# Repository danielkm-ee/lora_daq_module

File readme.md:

# LoRA DAQ Node
For our Electrical and Computer Engineering practicum at Portland State for 2025 we have developed a LoRA based data acquisition node that can be used for data collection and monitoring systems over large areas.

This board is powered by the Seeed Studios Wio-E5 LoRA module for use with it's designated antenna.

## Supported Peripherals
We've done our best to provide a versatile range of peripherals for high quality data collection and application flexibility. This includes a UART interface for communicating with the device via it's USB-C port, a SWD interface for loading and debugging applications, a 16-bit ADC and I2C connector that can be used with analog and I2C compatible sensors.

The device may be powered via it's USB-C (USB 2.0) connection, or by a 1s1p lithium ion battery. The device also
supports battery charging when powered by USB-C with the battery connected.

List of Peripherals
------------------
* 16-bit ADC
* I2C interface
* MicroSD card slot
* 2 external UART interfaces (one via USB-C port)
* 6-pin SWD header for ST-Link v2
* SMA connector for the 868-916MHz LoRA Antenna
* 2-pin JST EH connector for battery power and charging

## Credits
* Manaf Alali - hardware schematics
* Eyad Ahmed  - firmware
* Daniel Monahan - hardware schematics and layout
* Saleh Sabti - hardware schematics
* Dingyu Zhou - firmware

> All team members contributed to every aspect of the project, going beyond the general roles specified here.

----
*Portland State University ECE411 Practicum project, Fall 2025*

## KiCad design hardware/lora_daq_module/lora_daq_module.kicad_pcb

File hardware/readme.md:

# LoRA DAQ Hardware
Here you will find the KiCAD project files for the lora daq module. This project has been separated into three main parts:  
* `adc.kicad_sch` includes the input filter and supporting hardware related to the adc  
* `power_management.kicad_sch` includes the battery controller, ldos, and dc-dc converters  
* `lora_module.kicad_sch` includes the wio-e5, lora antennae, and eeprom  

## KiCAD Version Control Notes (Please read these!)
KiCAD version control will be managed through this git repository, there are some important things to 
keep track of while you work!  

### Git Management
To keep things nice, please keep all of your work confined to the schematic for your module. This should also 
correspond to your git branch. Here's an example:

Say I'm working on the ADC, first I'll make a git branch for my work...
```
$ git checkout -b schematic-adc
Switched to a new branch 'schematic-adc'
```
then I'll do work in the adc.kicad_sch file, and when I'm ready to submit the updated schematic I'll upload it to
my schematic branch.
```
$ git add ./adc.kicad_sch
$ git commit -m "added buffer to the input filter of the ads1115"
$ git push --set-upstream origin schematic-adc
Enumerating objects: 22, done.
Counting objects: 100% (22/22), done.
Delta compression using up to 14 threads
Compressing objects: 100% (20/20), done.
Writing objects: 100% (20/20), 8.72 KiB | 4.36 MiB/s, done.
Total 20 (delta 5), reused 0 (delta 0), pack-reused 0
remote: Resolving deltas: 100% (5/5), completed with 1 local object.
remote: 
remote: Create a pull request for 'test' on GitHub by visiting:
remote:      https://github.com/danielkm-ee/lora_daq_module/pull/new/schematic-adc
remote: 
To github.com:danielkm-ee/lora_daq_module.git
 * [new branch]      schematic-adc -> schematic-adc
Branch 'schematic-adc' set up to track remote branch 'schematic-adc' from 'origin'.
```
This way I can push/pull changes to the adc schematic separately, so I can safely work on the adc schematic without 
the need to resolve merge conflicts.

### Symbol and footprint libraries
When you are creating KiCAD symbols, they will be stored in your local *project* directory. We want these files to 
stay local to your machine until we can all collectively incorporate them into a project symbol library, so we've set 
up the .gitignore file to prevent accidental uploads of your local kicad schematic files, this includes symbols, 
footprints, and project settings related to your local UI.

> #### Files to keep local:
> * `fp-info-cache` -- this helps kicad pull up your most recent footprints faster, this thing is disposable and kicad creates and replaces it automatically
> * all `*.pretty` files -- these are footprint library files, they group your local symbols into library groups
> * all `*.kicad_mod` files -- these are your actual footprints (called 'modern footprint files')

> It is important that these aren't added to your commits because they will cause merge conflicts.

You are free to create and manage your footprint and symbol libraries locally in any way you choose--try to be 
organized because it will help us create a shared symbol library.

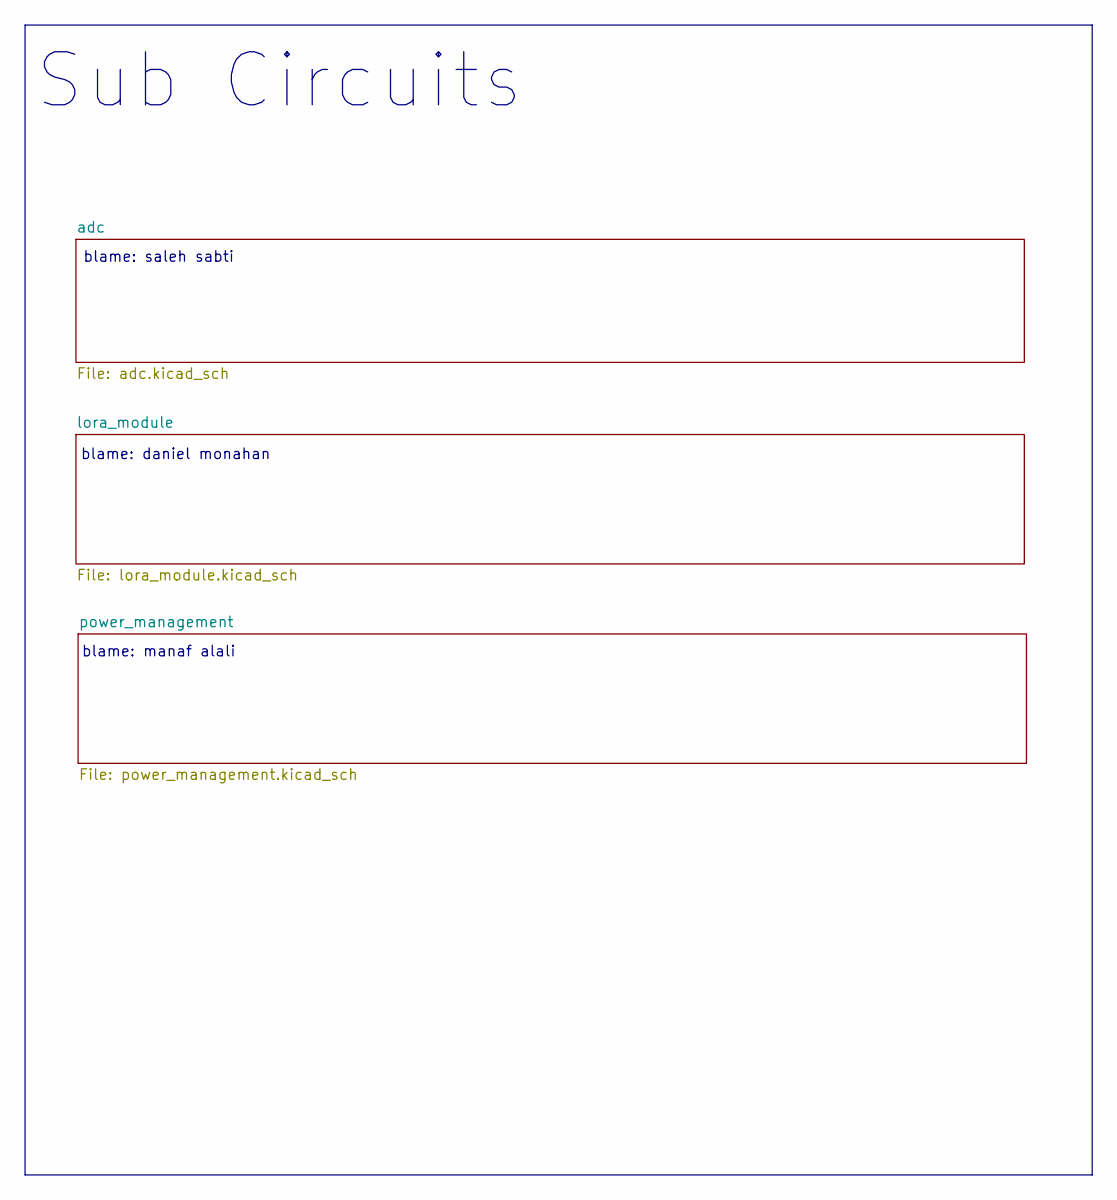
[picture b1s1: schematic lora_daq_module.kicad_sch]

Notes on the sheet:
blame: manaf alali
blame: saleh sabti
blame: daniel monahan
Sub Circuits

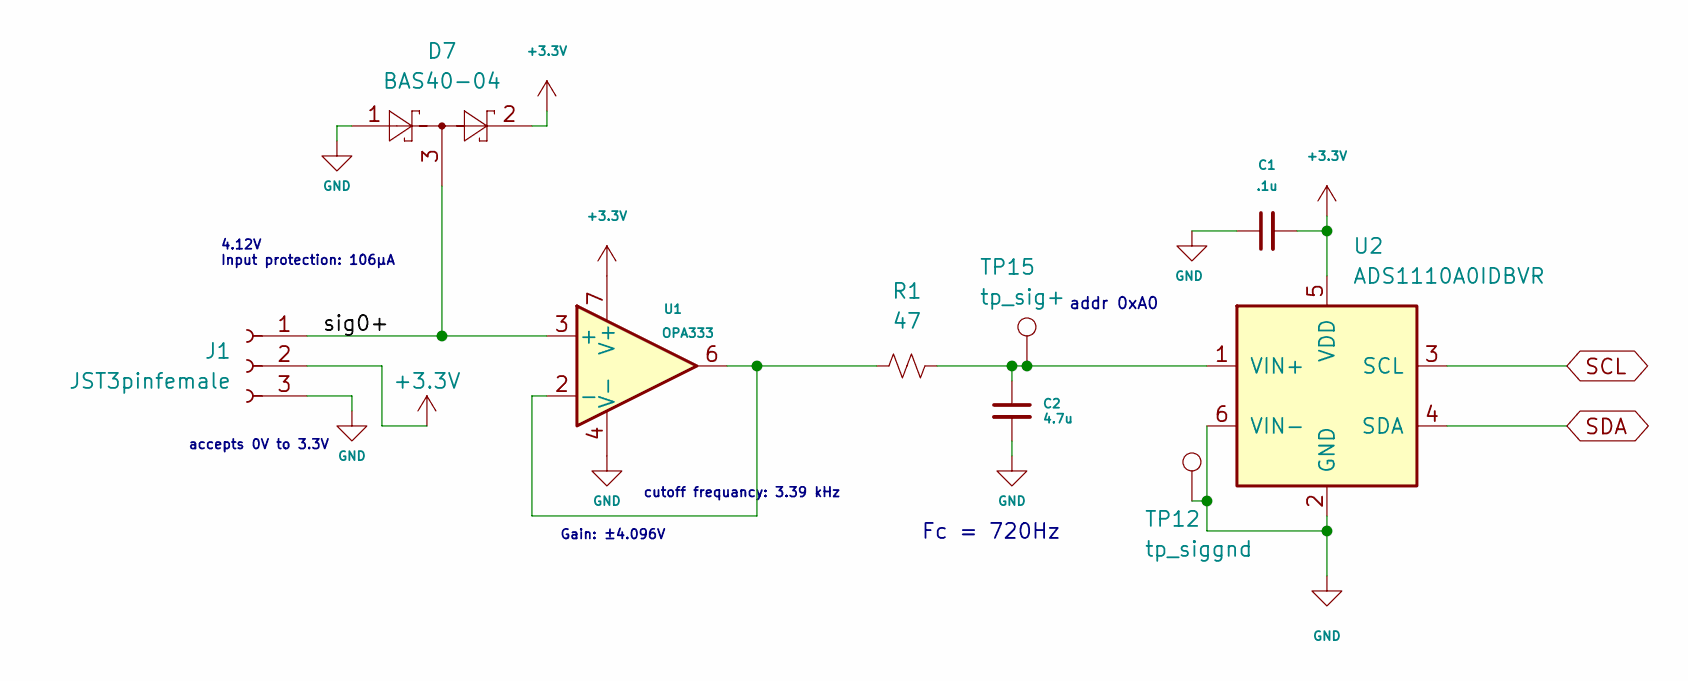
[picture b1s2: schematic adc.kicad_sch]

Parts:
C1: .1u; C_0603_1608Metric; Mfr PN CC0603KRX7R7BB104
C2: 4.7u; C_0603_1608Metric; Mfr PN CC0603KRX7R8BB473
D7: BAS40-04; SOT-23; Mfr PN BAS40-04
J1: JST3pinfemale; JST_EH_B3B-EH-A_1x03_P2.50mm_Vertical; Mfr PN B3B-EH-A
R1: 47; R_1206_3216Metric; Mfr PN RC1206FR-0747RL
TP12: tp_siggnd; TestPoint_THTPad_1.5x1.5mm_Drill0.7mm
TP15: tp_sig+; TestPoint_THTPad_1.5x1.5mm_Drill0.7mm
U1: OPA333; SOT-353_SC-70-5_Handsoldering; Mfr PN OPA333AIDCKR
U2: ADS1110A0IDBVR; SOT-23-6; Mfr PN ADS1110A0IDBVR

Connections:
+3.3V: C1.2, D7.2, J1.2, U1.7 (V+), U2.5 (VDD); also elsewhere on the board
/adc/sig0+: D7.3, J1.1, U1.3 (+)
GND: C1.1, C2.2, D7.1, J1.3, TP12.1, U1.4 (V-), U2.2 (GND), U2.6 (VIN-); also elsewhere on the board
unnamed: R1.1, U1.2 (-), U1.6
unnamed: C2.1, R1.2, TP15.1, U2.1 (VIN+)
SCL: U2.3 (SCL); also elsewhere on the board
SDA: U2.4 (SDA); also elsewhere on the board

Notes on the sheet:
addr 0xA0
cutoff frequancy: 3.39 kHz
accepts 0V to 3.3V
4.12V Input protection: 106µA
Gain: ±4.096V
Fc = 720Hz

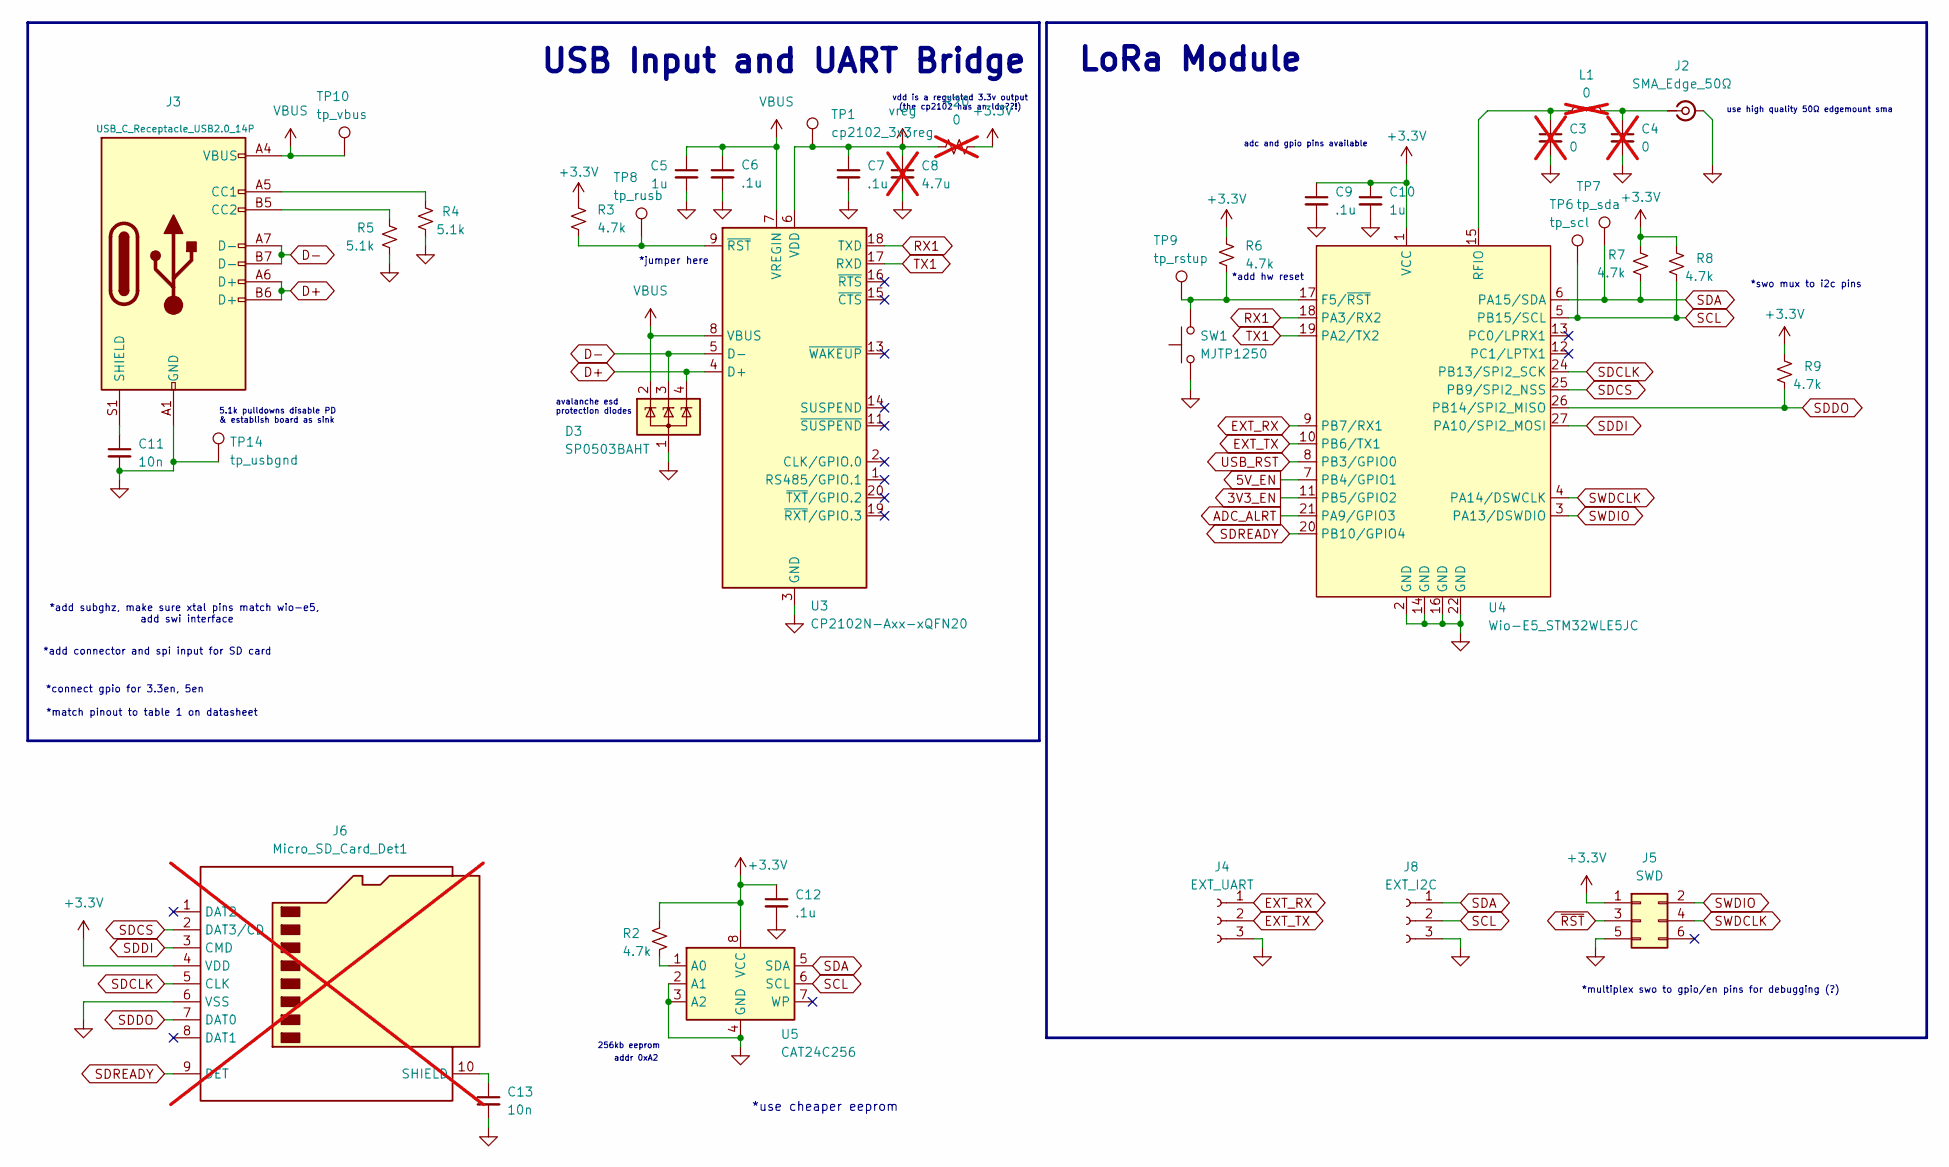
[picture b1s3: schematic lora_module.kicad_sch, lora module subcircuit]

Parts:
C3, C4: 0; C_0402_1005Metric; not fitted
C5, C10: 1u; C_0603_1608Metric; Mfr PN GCM188R71C105KA64D
C6, C7, C9, C12: .1u; C_0603_1608Metric; Mfr PN CC0603KRX7R7BB104
C8: 4.7u; C_1206_3216Metric; Mfr PN GRM31CR71H475KA12L; not fitted
C11, C13: 10n; C_0603_1608Metric; Mfr PN GCM188R72A103KA37D
D3: SP0503BAHT; SOT-143; Mfr PN SP0503BAHTG
J2: SMA_Edge_50Ω; SMA_Molex_73251-1153_EdgeMount_Horizontal; MPN CONSMA001-C-G
J3: USB_C_Receptacle_USB2.0_14P; USB_C_Receptacle_GCT_USB4105-xx-A_16P_TopMnt_Horizontal; Mfr PN USB4105-GF-A-120
J4: EXT_UART; JST_EH_B3B-EH-A_1x03_P2.50mm_Vertical; Mfr PN B3B-EH-A
J5: SWD; PinHeader_2x03_P2.54mm_Vertical; Mfr PN 61300621121
J6: Micro_SD_Card_Det1; microSD_HC_Molex_104031-0811; Mfr PN 1040310811; not fitted
J8: EXT_I2C; JST_EH_B3B-EH-A_1x03_P2.50mm_Vertical; Mfr PN B3B-EH-A
L1: 0; L_0402_1005Metric; Mfr PN RC0402JR-070RL; not fitted
R2, R3, R6, R7, R8, R9: 4.7k; R_0603_1608Metric; Mfr PN RC0603JR-074K7L
R4, R5: 5.1k; R_0603_1608Metric; Mfr PN RC0603FR-075K1L
R20: 0; R_0603_1608Metric; Mfr PN RMCF0603ZT0R00; not fitted
SW1: MJTP1250; SW_PUSH_1P1T_6x3.5mm_H5.0_APEM_MJTP1250; Mfr PN MJTP1250
TP1: cp2102_3v3reg; TestPoint_Pad_1.5x1.5mm
TP6: tp_scl; TestPoint_THTPad_1.5x1.5mm_Drill0.7mm
TP7: tp_sda; TestPoint_THTPad_1.5x1.5mm_Drill0.7mm
TP8: tp_rusb; TestPoint_THTPad_1.5x1.5mm_Drill0.7mm
TP9: tp_rstup; TestPoint_THTPad_1.5x1.5mm_Drill0.7mm
TP10: tp_vbus; TestPoint_THTPad_1.5x1.5mm_Drill0.7mm
TP14: tp_usbgnd; TestPoint_THTPad_1.5x1.5mm_Drill0.7mm
U3: CP2102N-Axx-xQFN20; SiliconLabs_QFN-20-1EP_3x3mm_P0.5mm_EP1.8x1.8mm; Mfr PN CP2102N-A02-GQFN20R
U4: Wio-E5_STM32WLE5JC; LoRa-E5; Mfr PN 317990829
U5: CAT24C256; SOIC-8-1EP_3.9x4.9mm_P1.27mm_EP2.29x3mm; Mfr PN CAT24C256WI-GT3

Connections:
3V3_EN: U4.11 (PB5/GPIO2)
5V_EN: U4.7 (PB4/GPIO1)
+3.3V: C9.1, C10.1, C12.1, J5.1, J6.4 (VDD), R2.2, R3.1, R6.1, R7.2, R8.2, R9.2, R20.2, U4.1 (VCC), U5.8 (VCC); also elsewhere on the board
ADC_ALRT: U4.21 (PA9/GPIO3)
D+: D3.4 (K), J3.A6 (D+), J3.B6 (D+), U3.4 (D+)
D-: D3.3 (K), J3.A7 (D-), J3.B7 (D-), U3.5 (D-)
EXT_RX: J4.1, U4.9 (PB7/RX1)
EXT_TX: J4.2, U4.10 (PB6/TX1)
GND: C3.2, C4.2, C5.2, C6.2, C7.2, C8.2, C9.2, C10.2, C11.2, C12.2, C13.2, D3.1 (A), J2.2 (Ext), J3.A1 (GND), J3.A12 (GND), J3.B1 (GND), J3.B12 (GND), J4.3, J5.5, J6.6 (VSS), J8.3, R4.1, R5.1, SW1.1, TP14.1, U3.3 (GND), U3.12 (GND), U3.21 (GND), U4.2 (GND), U4.14 (GND), U4.16 (GND), U4.22 (GND), U5.2 (A1), U5.3 (A2), U5.4 (GND); also elsewhere on the board
unnamed: C4.1, J2.1 (In), L1.2
unnamed: J3.A5 (CC1), R4.2
unnamed: J3.B5 (CC2), R5.2
unnamed: C11.1, J3.S1 (SHIELD)
unnamed: C13.1, J6.10 (SHIELD)
unnamed: R3.2, TP8.1, U3.9 (~RST)
unnamed: R6.2, SW1.2, TP9.1, U4.17 (F5/~RST)
unnamed: C3.1, L1.1, U4.15 (RFIO)
unnamed: R2.1, U5.1 (A0)
RX1: U3.18 (TXD), U4.18 (PA3/RX2)
SCL: J8.2, R8.1, U4.5 (PB15/SCL), U5.6 (SCL); also elsewhere on the board
SDA: J8.1, R7.1, U4.6 (PA15/SDA), U5.5 (SDA); also elsewhere on the board
SDCLK: J6.5 (CLK), U4.24 (PB13/SPI2_SCK)
SDCS: J6.2 (DAT3/CD), U4.25 (PB9/SPI2_NSS)
SDDI: J6.3 (CMD), U4.27 (PA10/SPI2_MOSI)
SDDO: J6.7 (DAT0), R9.1, U4.26 (PB14/SPI2_MISO)
SDREADY: J6.9 (DET), U4.20 (PB10/GPIO4)
SWDCLK: J5.4, U4.4 (PA14/DSWCLK)
SWDIO: J5.2, U4.3 (PA13/DSWDIO)
TX1: U3.17 (RXD), U4.19 (PA2/TX2)
USB_RST: U4.8 (PB3/GPIO0)
VBUS: C5.1, C6.1, D3.2 (K), J3.A4 (VBUS), J3.A9 (VBUS), J3.B4 (VBUS), J3.B9 (VBUS), TP10.1, U3.7 (VREGIN), U3.8 (VBUS); also elsewhere on the board
vreg: C7.1, C8.1, R20.1, TP1.1, U3.6 (VDD)
~RST: J5.3

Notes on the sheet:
vdd is a regulated 3.3v output (the cp2102 has an ldo??!)
*use cheaper eeprom
avalanche esd protection diodes
5.1k pulldowns disable PD & establish board as sink
*jumper here
*match pinout to table 1 on datasheet
*add hw reset
use high quality 50Ω edgemount sma
USB Input and UART Bridge
*swo mux to i2c pins
256kb eeprom
*add subghz, make sure xtal pins match wio-e5, add swi interface
addr 0xA2
*add connector and spi input for SD card
LoRa Module
*connect gpio for 3.3en, 5en
adc and gpio pins available
*multiplex swo to gpio/en pins for debugging (?)

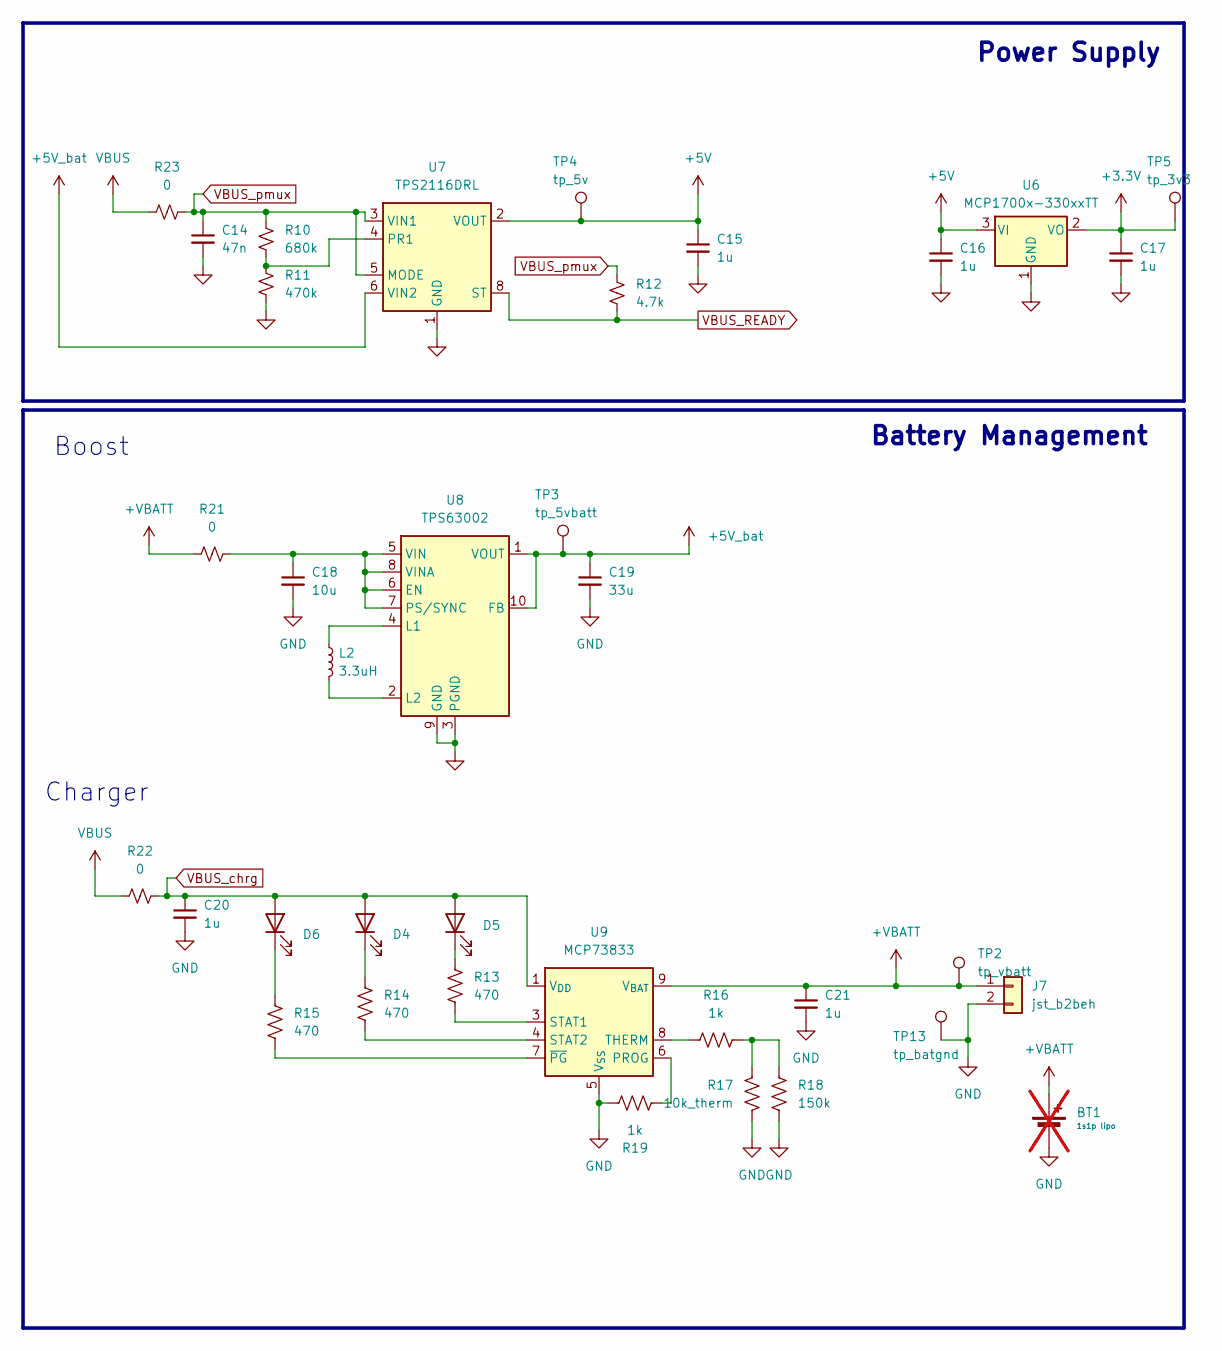
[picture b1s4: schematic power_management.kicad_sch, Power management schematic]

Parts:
BT1: 1s1p lipo; Mfr PN 258; not fitted
C14: 47n; C_0603_1608Metric; Mfr PN CC0603KRX7R8BB473
C15, C16, C17, C20, C21: 1u; C_0603_1608Metric; Mfr PN GCM188R71C105KA64D
C18: 10u; C_1206_3216Metric; Mfr PN CL31A106KBHNNNE
C19: 33u; C_1206_3216Metric; Mfr PN C3216JB1C336M160AB
D4: Green; LED_0603_1608Metric; Mfr PN LTST-C191KGKT
D5: Yellow; LED_0603_1608Metric; Mfr PN LTST-C191KSKT
D6: Red; LED_0603_1608Metric; Mfr PN LTST-C190KRKT
J7: jst_b2beh; JST_EH_B2B-EH-A_1x02_P2.50mm_Vertical; Mfr PN B2B-EH-A
L2: 3.3uH; L_Coilcraft_LPS3010; Mfr PN LPS3015-332MRC
R10: 680k; R_0603_1608Metric; Mfr PN RC0603FR-07680KL
R11: 470k; R_0603_1608Metric; Mfr PN RMCF0603FT470K
R12: 4.7k; R_0603_1608Metric; Mfr PN RC0603JR-074K7L
R13, R14, R15: 470; R_0603_1608Metric; Mfr PN RC0603JR-07470RL
R16, R19: 1k; R_0603_1608Metric; Mfr PN RMCF0603FT1K00
R17: 10k_therm; R_0603_1608Metric; Mfr PN NCU18XH103F60RB
R18: 150k; R_0603_1608Metric; Mfr PN RMCF0603FT150K
R21, R22, R23: 0; R_1812_4532Metric; Mfr PN ERJ-12Y0R00U
TP2: tp_vbatt; TestPoint_THTPad_1.5x1.5mm_Drill0.7mm
TP3: tp_5vbatt; TestPoint_THTPad_1.5x1.5mm_Drill0.7mm
TP4: tp_5v; TestPoint_THTPad_1.5x1.5mm_Drill0.7mm
TP5: tp_3v3; TestPoint_THTPad_1.5x1.5mm_Drill0.7mm
TP13: tp_batgnd; TestPoint_THTPad_1.5x1.5mm_Drill0.7mm
U6: MCP1700x-330xxTT; SOT-23; Mfr PN MCP1700T-3302E/TT
U7: TPS2116DRL; SOT-583-8; Mfr PN TPS2116DRLR
U8: TPS63002; Texas_DRC0010J_ThermalVias; Mfr PN TPS63002DRCR
U9: MCP73833; MSOP-10_3x3mm_P0.5mm; Mfr PN MCP73833T-AMI/UN

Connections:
+3.3V: C17.1, TP5.1, U6.2 (VO); also elsewhere on the board
+5V: C15.1, C16.1, TP4.1, U6.3 (VI), U7.2 (VOUT), U7.7 (VOUT)
+5V_bat: C19.1, TP3.1, U7.6 (VIN2), U8.1 (VOUT), U8.10 (FB)
+VBATT: BT1.1 (+), C21.1, J7.1, R21.1, TP2.1, U9.9 (V_{BAT}), U9.10 (V_{BAT})
GND: C14.2, C15.2, C16.2, C17.2, C18.2, C19.2, C20.2, C21.2, J7.2, R11.2, R17.2, R18.1, R19.1, TP13.1, U6.1 (GND), U7.1 (GND), U8.3 (PGND), U8.9 (GND), U8.11 (PGND), U9.5 (V_{SS}); also elsewhere on the board
unnamed: D4.1 (K), R14.1
unnamed: D5.1 (K), R13.1
unnamed: D6.1 (K), R15.1
unnamed: R16.2, R17.1, R18.2
unnamed: R10.2, R11.1, U7.4 (PR1)
unnamed: C18.1, R21.2, U8.5 (VIN), U8.6 (EN), U8.7 (PS/SYNC), U8.8 (VINA)
unnamed: L2.1, U8.4 (L1)
unnamed: L2.2, U8.2 (L2)
unnamed: R19.2, U9.6 (PROG)
unnamed: R13.2, U9.3 (STAT1)
unnamed: R14.2, U9.4 (STAT2)
unnamed: R16.1, U9.8 (THERM)
unnamed: R15.2, U9.7 (~PG)
VBUS: R22.1, R23.1; also elsewhere on the board
VBUS_READY: R12.2, U7.8 (ST)
VBUS_chrg: C20.1, D4.2 (A), D5.2 (A), D6.2 (A), R22.2, U9.1 (V_{DD}), U9.2 (V_{DD})
VBUS_pmux: C14.1, R10.1, R12.1, R23.2, U7.3 (VIN1), U7.5 (MODE)

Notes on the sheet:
Boost
Battery Management
Charger
Power Supply

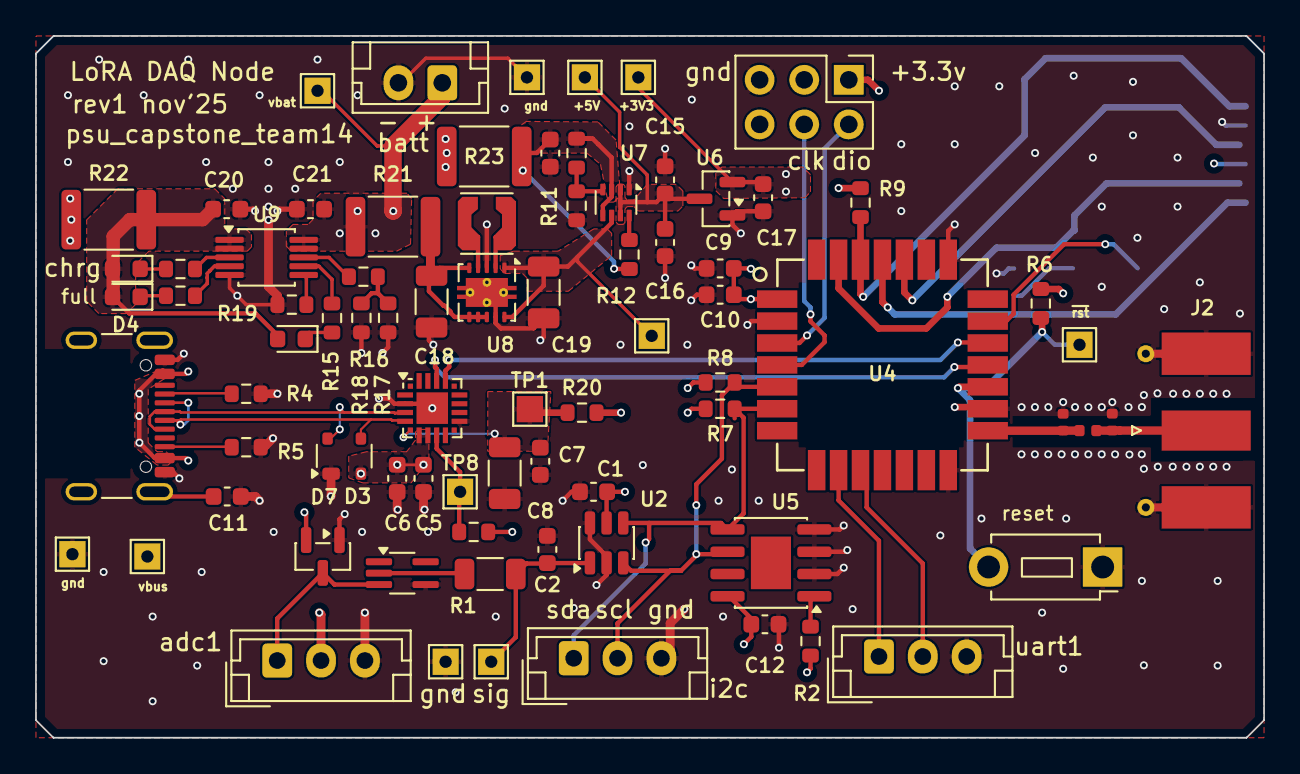
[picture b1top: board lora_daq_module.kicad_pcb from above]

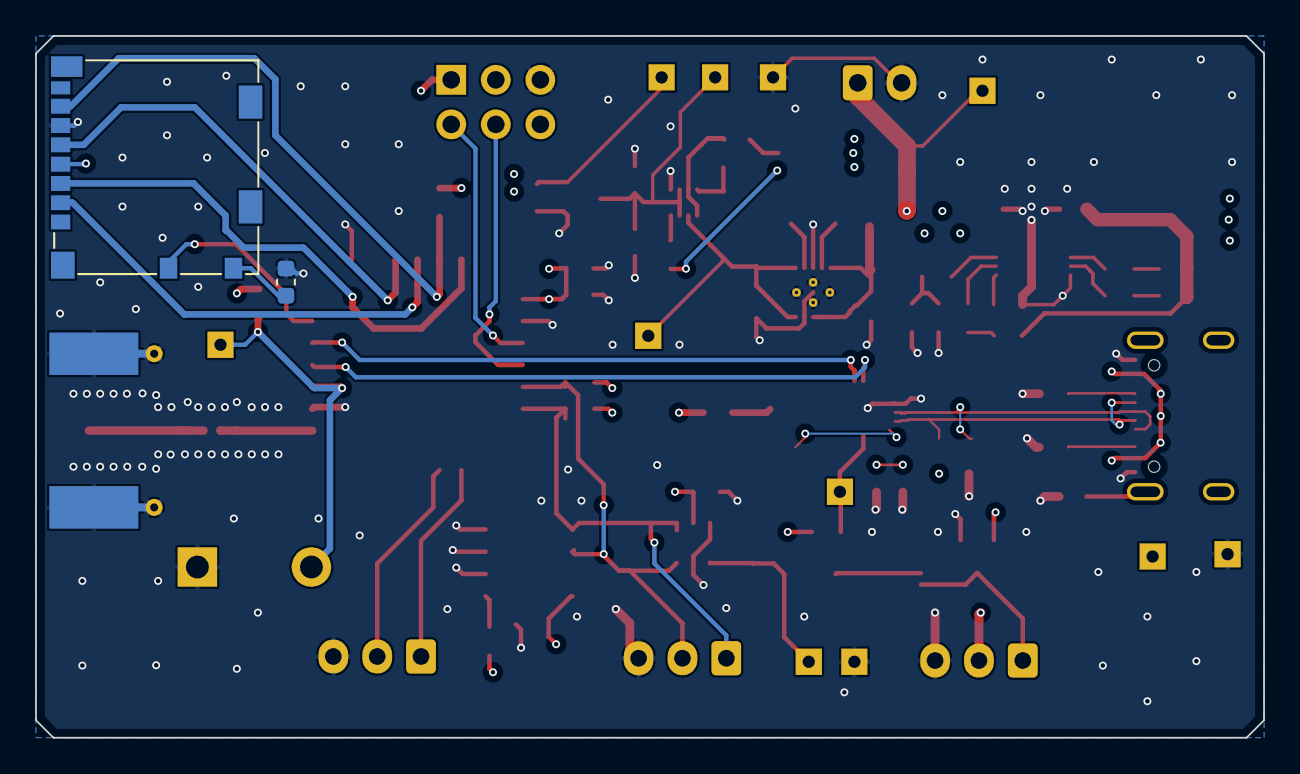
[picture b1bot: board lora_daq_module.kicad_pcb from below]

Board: 4 copper layers, 70.0 x 40.0 mm, 81 parts (2 on the bottom side), 50 nets.

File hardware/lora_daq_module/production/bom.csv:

Designator,Footprint,Quantity,Value,LCSC Part #
"C1, C12, C6, C7, C9",0603,5,.1u,
"C10, C15, C16, C17, C20, C21, C5",0603,7,1u,
"C11, C13",0603,2,10n,
C14,0603,1,47n,
C18,1206,1,10u,
C19,1206,1,33u,
C2,0603,1,4.7u,
C8,1206,1,4.7u,
D3,SOT-143,1,SP0503BAHT,
D4,0603,1,Green,
D5,0603,1,Yellow,
D6,0603,1,Red,
D7,SOT-23,1,BAS40-04,
J1,JST_EH_B3B-EH-A_1x03_P2.50mm_Vertical,1,JST3pinfemale,
J2,SMA_Molex_73251-1153_EdgeMount_Horizontal,1,SMA_Edge_50Ω,CONSMA001-C-G
J3,USB_C_Receptacle_GCT_USB4105-xx-A_16P_TopMnt_Horizontal,1,USB_C_Receptacle_USB2.0_14P,
J4,JST_EH_B3B-EH-A_1x03_P2.50mm_Vertical,1,EXT_UART,
J5,PinHeader_2x03_P2.54mm_Vertical,1,SWD,
J6,microSD_HC_Molex_104031-0811,1,Micro_SD_Card_Det1,
J7,JST_EH_B2B-EH-A_1x02_P2.50mm_Vertical,1,jst_b2beh,
J8,JST_EH_B3B-EH-A_1x03_P2.50mm_Vertical,1,EXT_I2C,
L1,0402,1,0,
L2,L_Coilcraft_LPS3010,1,3.3uH,
R1,1206,1,47,
R10,0603,1,680k,
R11,0603,1,470k,
"R12, R2, R3, R6, R7, R8, R9",0603,7,4.7k,
"R13, R14, R15",0603,3,470,
"R16, R19",0603,2,1k,
R17,0603,1,10k_therm,
R18,0603,1,150k,
R20,0603,1,0,
"R21, R22, R23",1812,3,0,
"R4, R5",0603,2,5.1k,
SW1,SW_PUSH_1P1T_6x3.5mm_H5.0_APEM_MJTP1250,1,MJTP1250,
TP10,TestPoint_THTPad_1.5x1.5mm_Drill0.7mm,1,tp_vbus,
TP12,TestPoint_THTPad_1.5x1.5mm_Drill0.7mm,1,tp_siggnd,
TP13,TestPoint_THTPad_1.5x1.5mm_Drill0.7mm,1,tp_batgnd,
TP14,TestPoint_THTPad_1.5x1.5mm_Drill0.7mm,1,tp_usbgnd,
TP15,TestPoint_THTPad_1.5x1.5mm_Drill0.7mm,1,tp_sig+,
TP2,TestPoint_THTPad_1.5x1.5mm_Drill0.7mm,1,tp_vbatt,
TP3,TestPoint_THTPad_1.5x1.5mm_Drill0.7mm,1,tp_5vbatt,
TP4,TestPoint_THTPad_1.5x1.5mm_Drill0.7mm,1,tp_5v,
TP5,TestPoint_THTPad_1.5x1.5mm_Drill0.7mm,1,tp_3v3,
TP8,TestPoint_THTPad_1.5x1.5mm_Drill0.7mm,1,tp_rusb,
TP9,TestPoint_THTPad_1.5x1.5mm_Drill0.7mm,1,tp_rstup,
U1,SOT-353_SC-70-5_Handsoldering,1,OPA333,
U2,SOT-23-6,1,ADS1110A0IDBVR,
U3,SiliconLabs_QFN-20-1EP_3x3mm_P0.5mm_EP1.8x1.8mm,1,CP2102N-Axx-xQFN20,
U4,LoRa-E5,1,Wio-E5_STM32WLE5JC,
U5,SOIC-8-1EP_3.9x4.9mm_P1.27mm_EP2.29x3mm,1,CAT24C256,
U6,SOT-23,1,MCP1700x-330xxTT,
U7,SOT-583-8,1,TPS2116DRL,
U8,Texas_DRC0010J_ThermalVias,1,TPS63002,
U9,MSOP-10_3x3mm_P0.5mm,1,MCP73833,

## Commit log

2025-10-09 inital commit, add project structure/readmes
2025-10-09 add firmware structure
2025-10-09 add prelim license
2025-10-09 update license
2025-10-16 add .gitignore to prevent local kicad configs which will cause merge issues
2025-10-16 add *-backups to git ignore
2025-10-16 add kicad project files
2025-10-16 add idea for kicad version control to readme
2025-10-16 add docs folder for dev notes and other official stuff
2025-10-16 update schematic properties
2025-10-21 add dev notes for adc integration
2025-10-21 add dev notes for power schematic
2025-10-24 add chips and start wiring USBC Recept. & UART bridge
2025-10-24 added eeprom support, antenna connector, and general connections needed for rev0 schematic
2025-10-24 schematic documentation
2025-10-27 added ADC input filter schematic
2025-10-27 added Oct 26 ADC KiCad schematic design notes
2025-10-28 added Oct 26 ADC schematic design log
2025-10-28 added the mcp73833
2025-10-29 added the tps63001 and tps63002 with their reference design
2025-10-30 Updated the Adc circuit w/filters
2025-11-11 docs: voltage divider optimization notes Nov 10
2025-11-11 modified ADC input filter schematic
2025-11-11 post design review comments
2025-11-12 initial commit of working toolchain
2025-11-12 clean up readme
2025-11-12 adjusted ADC input filter power rails, added commets
2025-11-12 add pinout for wio-e5 and add entry about schematic revisions to the dev note
2025-11-12 add sd card, swd connector, external uart, and update pinout for wio-e5
2025-11-12 add kicad symbol for wio-e5
2025-11-12 Removed the 3.3V buck-boost converter from the original design, then added LDO
2025-11-12 remove backups from repo
2025-11-13 update dev notes, add prelim layout pdf, prelim layout cad as pngs, and updated schematic as pdf
2025-11-13 add library for wio-e5 (from seeed studio, does not include custom wio-e5 symbol)
2025-11-13 updated power schematic to include power switching IC for battery/usb power, minor changes to lora module schematic, added footprints to all component and began with the preliminary layout based on d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
2025-11-13 update readme and description
2025-11-13 setup BOM columns
2025-11-14 add preliminary bom as xlsx, update dev notes regarding bom decision making process
2025-11-14 assign parts and update BOM in symbol field table, warn: pcb footprints need update
2025-11-14 add prelim bom as csv for native viewing on github
2025-11-15 solve strange Makefile problems
2025-11-16 add functional_decomposition doc
2025-11-16 near-complete layout of power domain
2025-11-17 lay traces to all components
2025-11-17 finish rough layout, drc fixedup
2025-11-17 add pdf captures of rough layout
2025-11-17 add rough draft schematic
2025-11-18 add test points and antenna microstrip
2025-11-18 add notes regarding antenna microstrip design
2025-11-20 add FreeRTOS lib
2025-11-20 edit board setup for jlcpcb 4 layer 1.6mm 1oz copper in/out and redesign antenna microstrip
2025-11-20 add ohm resistors for power schematic, update design rules for jlc
2025-11-21 add pcb final revision dev notes
2025-11-21 add final schematics, layout, 3dmodels
2025-11-21 add 0Ω resistors for disabling power circuits, revise adc input buffer and filter based on design review feedback, revise microstrip trace, add hardware reset button, add i2c connector and jst recept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
2025-11-21 add production files used for jlc order
2025-11-22 add rough draft of project readme
2025-11-22 update rough draft of readme
2025-11-25 adopting lora module from offical repo
2025-11-27 fix: strange compile issue after adding FreeRTOS, decide to test without FreeRTOS.
2025-12-01 enable lora, timer interrupt scheduling main structure and layout for src structure
2025-12-01 update readme for files structure, lora, and scheduling
2025-12-01 fix readme typos
2025-12-02 add CI test and format checker test
2025-12-02 update CI test worker version
2025-12-02 add I2C interface
2025-12-03 add rx firmware and test our tx is working fine
2025-12-04 Add GPIO driver, ADS1110 ADC, and board config system
2025-12-04 add new uart
2025-12-06 fix interrupt issues during initializing timmer
2025-12-06 fix: using uart building from HAL instead, not relying on example driver... That brings robotness of changing UART peripheral much easier; remove gpio mode Macro as this has delared everywhere
2025-12-06 add ADC application code; test once with our analog sensor but keep reading the same value
2025-12-12 fix rx compile issue
2025-12-12 fix format
2025-12-12 Clean commit with all changes with merge with main, fix format checker
2025-12-12 add Board ID config
2025-12-12 add time stamp at secs
2025-12-12 remove docs from external dependancy
